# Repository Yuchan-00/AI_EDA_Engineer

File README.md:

# AI EDA ENGINEER

**English** · [한국어](README.ko.md)

A **verification-first** AI engineering system for electronic circuit design. It takes a natural-language requirement through one pipeline:

`requirements` → `parts & regulatory research` → `Universal Circuit IR` → `calculations / SPICE` → `KiCad schematic & PCB` → `ERC / DRC` → `manufacturing outputs` → `independent review` → `auto-fix`

> **Core principle: the LLM never decides design truth.** It only proposes and orchestrates. Facts come from the IR, provenance, deterministic tools (calculators, SPICE, KiCad ERC/DRC, manufacturing-file checks) and an independent reviewer.

This page is an English overview. The full reference — every stage, check, option, measured result and the change history — is the Korean [README.ko.md](README.ko.md). The generated stage reports and the local web GUI are in Korean; the read-only HTML report (`ai-eda report`) is in English.

## Quick install

**macOS / Linux (Ubuntu, Debian, Arch, Fedora)** — in a terminal:

```bash
curl -fsSL https://raw.githubusercontent.com/Yuchan-00/AI_EDA_Engineer/main/install.sh | bash
```

**Windows 10 / 11** — in PowerShell:

```powershell
powershell -ExecutionPolicy Bypass -c "irm https://raw.githubusercontent.com/Yuchan-00/AI_EDA_Engineer/main/install.ps1 | iex"
```

If you already have the repository, run `./install.sh` (macOS / Linux) or `install.cmd` (Windows) in its folder.

- The installer sets up a uv-managed Python 3.12 environment, KiCad 10 (with libraries) and ngspice without asking. A browser for PDF reports is installed only on Linux when none is found; macOS and Windows use an existing Chrome or Edge.
- It puts `ai-eda` on your PATH and finishes with `ai-eda selftest`, which designs a 12 V → 5 V divider end to end to confirm the tools actually run.
- Do not run it with `sudo`; the script asks for an administrator password itself when it needs one (UAC on Windows).
- Debian stable has no KiCad 10 package: install with `--no-kicad`, then install KiCad 10 yourself. Options and per-OS details are in the Korean README (설치).

Then open a new terminal:

```bash
ai-eda doctor       # tools found (KiCad, ngspice, browser) and how to install what is missing
ai-eda gui --open   # local web GUI (Korean)
```

The install CI (GitHub Actions, 2026-10-14) installs, runs `doctor --strict` and `selftest` on ubuntu-24.04, ubuntu-22.04, macos-15, Arch Linux and windows-2025; on all five the selftest's divider board passed KiCad ERC/DRC with 0 errors / 0 warnings.

## Usage

```bash
ai-eda new demo --request "a circuit that converts 12 V input to 5 V"
ai-eda run projects/demo/ir.json
```

When required information is missing, the pipeline stops at `USER_INPUT_REQUIRED` and prints its questions. Answer with `--answer key=value` and run again:

```bash
ai-eda run projects/demo/ir.json --answer application="bench supply" --answer jurisdiction=EU \
  --answer input_voltage="12 V" --answer output_voltage="5 V"
```

A template's free choices (for example the divider's R2) are shown in a `confirm_design` table and applied only after you confirm it on a later run with `--answer confirm_design=yes`. Other commands: `review`, `report` / `serve` (read-only HTML report), `stage-reports` (Korean stage reports as Markdown, HTML and PDF), `relocate` (re-record a copied or moved project), `setup-kicad`.

## What it does

| Layer | What it is |
|---|---|
| **Universal Circuit IR** | Pydantic v2 model of the project, requirements, components, pins, nets, topology, constraints, PCB, regulatory scope, validation and artifacts. The design hash covers design content only, so the same design gets the same hash anywhere. |
| **Provenance** | Every important value is `Traced[T]`: `user_requirement`, `authoritative`, `assumption`, `derived` or `llm_generated`. |
| **Validation status** | `PASS / FAIL / NOT_VERIFIED / NOT_APPLICABLE / USER_INPUT_REQUIRED / UNRESOLVED`, aggregated conservatively. No evidence means `NOT_VERIFIED`, never `PASS`. |
| **Calculators** | Deterministic, registered calculators (Ohm's law, dividers, RC, LED resistors, power, junction temperature, transmission lines, RF matching and filters, ...) whose results are recomputed and checked. |
| **SPICE** | ngspice through KiCad's bundled library (ctypes): operating point, DC sweep, transient and AC analyses, judged against expected values with explicit tolerances or one-sided bounds. |
| **KiCad** | Compilers from the IR to `.kicad_sch`, `.kicad_pcb` and `.kicad_pro`, using symbols and footprints read from the installed KiCad libraries (never from model memory); ERC/DRC through `kicad-cli`, where any violation, warnings included, is a FAIL. |
| **Layout** | Deterministic placement (grid, core-ring, RF floorplan), a grid maze router with negotiated congestion, silkscreen placement, a built-in 3D preview, and need-driven signal-integrity checks (impedance, critical length, RF length). |
| **Manufacturing** | Gerber / drill export with format checks, BOM and CPL, and fab-capability limits grounded verbatim from an archived vendor page. |
| **Parts & regulatory** | Part existence checks against libraries and archived datasheets, datasheet-fact grounding, catalog import, and curated regulatory candidates (EU and KR) with deterministic applicability. Sources are fetched only with `--online` from trusted origins and archived with sha256. Regulatory *compliance* is never claimed (`NOT_VERIFIED`). |
| **Templates** | Deterministic circuit templates: unloaded resistor divider, LED + series resistor, first-order RC low-pass, BJT astable, ATmega128 dev board, and five KR 447 MHz radio boards (`radio_build`). |
| **Agents & LLM** | Ten agents that only propose; the orchestrator validates and applies proposals. LLMs (OpenRouter with a budget flag as approval, or your local Claude Code CLI) extract requirements and suggest parts; every model output must be grounded and then confirmed by you on a later run before it enters the IR. |
| **Review & repair** | An independent reviewer covering 14 areas, and an auto-repair loop that only regenerates artifacts or re-runs tools. Design changes need a human. |
| **Approval gate** | Outward-facing actions (paid model calls, network fetches, secrets, git push, orders, submissions) go through an explicit approval gate. |

## Known limits

- Component suitability is judged for electrical stress only (nominal values, one operating point, one temperature). Safety, regulatory compliance, environment, reliability, manufacturability, sourcing and cost are not evaluated by any code.
- Several KiCad canary tests (silkscreen DRC, 3D export, sibling project rules) have not yet run on a KiCad machine; until they do, the checks that depend on them stay `NOT_VERIFIED` by design. The only routed board whose real DRC has run is the selftest's divider in the install CI.
- Board impedance is computed quasi-statically and losslessly; only a fab's coupon measurement can confirm it.

The full list, with the reason each limit exists, is in [README.ko.md](README.ko.md).

## Project layout

```
ai_eda/
  ir/            Universal Circuit IR, provenance, validation status
  validation/    validators and their registry
  design/        deterministic circuit templates (rf/: KR 447 MHz radio family)
  tools/         calculators, ngspice runner, KiCad parser / libraries / kicad-cli wrapper,
                 placement, routing, silkscreen, 3D preview, manufacturing, source archive
  parts/         part existence, identity grounding, datasheet facts, catalog
  regulatory/    curated candidates, applicability, official-source research
  compilers/     IR → .kicad_sch / .kicad_pcb / .kicad_pro / BOM / CPL / SPICE netlist
  agents/        agents (propose only)
  llm/           model layer (OpenRouter, Claude Code CLI, budget, extraction)
  review/        independent reviewer (14 areas)
  repair/        deterministic repair strategies and closed loop
  report/, gui/  read-only HTML report, Korean stage reports, local web GUI
  workflow/      19-stage pipeline and orchestrator
  security/      approval gate for outward-facing actions
  cli.py         doctor / setup-kicad / selftest / new / run / review / relocate / report / serve / stage-reports / gui
tests/           test suite (tool tests skip when KiCad / ngspice are missing)
docs/ARCHITECTURE.md   spec ↔ module map and invariants (Korean)
install.sh, install.ps1, install.cmd   one-line installers
```

Run the tests with `python -m pytest -q -p no:cacheprovider -rs`. Without KiCad and ngspice the tool tests skip, and a green run without them is not tool verification.

## License

MIT License with the Commons Clause License Condition v1.0, see [LICENSE](LICENSE). You may use, copy, modify and share this software free of charge; you may not sell it, or a product or service whose value comes substantially from it (hosting and paid support included), without a separate agreement with the author. Because of that restriction it is source-available rather than OSI-approved open source.

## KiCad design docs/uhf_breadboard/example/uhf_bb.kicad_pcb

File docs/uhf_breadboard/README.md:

# UHF FM 무전기 (만능기판·브레드보드 실험용, 아마추어 430–440 MHz)

이 문서는 `radio_build = uhf_breadboard` 템플릿(`ai_eda/design/rf/t_breadboard.py`)이 만드는 무전기를 손으로 조립하기 위한 안내서입니다. 상용급이 아니라 **실험해서 동작을 확인하는 수준**이 목표입니다. 프로그래머블 소자(마이컴, PLL, FM 송수신 모듈)는 쓰지 않고, 트랜지스터와 연산증폭기로만 만듭니다.

> **먼저 읽을 것 — 법규**
> - 직접 만든 송신기는 KC 적합성평가를 받지 않았습니다. **생활무선(447 MHz 면허 면제) 채널에서는 절대 송신하지 않습니다.**
> - 이 무전기는 **아마추어 무선국 허가** 조건 안에서, 430–440 MHz 아마추어 대역의 허가된 주파수·출력·전파형식으로만 씁니다. 국내 아마추어 대역 사용계획과 허가 조건은 이 문서에서 확인하지 못했습니다 [UNVERIFIED].
> - 안테나를 달기 전에 반드시 **50 Ω 더미로드**에 연결하고 불요발사(스퓨리어스)를 확인합니다(아래 조정 순서 6단계).

## 1. 전체 구성

```
           ┌──────────── 송신 (TX/RX 스위치를 TX로) ─────────────────────────────────────────────┐
 마이크 → TL071 증폭(+다이오드 리미터) → TL071 저역통과(3 kHz) → 편이 트리머 → 가변용량 다이오드
                                                                                │
   36 MHz 수정 VXO(2N3904) → ×3 BF199(108 MHz) → ×2 BFR92A(216 MHz) → ×2 BFR92A(432 MHz)
   → 3공진기 대역통과 → A급 출력단 BFR92A(약 30 mW) → L 정합 → 5차 저역통과 → T/R 스위치 → SMA
                                                                                │
           ┌──────────── 수신 (TX/RX 스위치를 RX로) ────────────────────────────┘
 SMA → T/R(λ/4) → 공통 베이스 RF 증폭 BFR92A → 초재생 검파 BFR92A(자기 소멸 약 190 kHz)
     → TL071 증폭 → TL071 저역통과(3 kHz, 소멸 신호 제거) → 볼륨 → TL071 + BD139/BD140 → 스피커 8 Ω
```

| 블록 | 부품 번호 | 내용 |
|---|---|---|
| 전원 | 1xx | 9 V 배터리, 전원 스위치, 1N5817(역접속 보호), TX/RX 슬라이드 스위치, L78L05 두 개(V5T 송신용, V5R 수신용) |
| 송신 오디오 | 2xx | 일렉트릿 마이크, TL071 ×2, 소프트 리미터 1N4148 ×2, 편이 트리머 RV201, 가변용량 바이어스 |
| 송신 RF | 3xx | 수정 VXO, ×3·×2·×2 체배기, 3공진기 대역통과(CT304–CT306), 출력단, L 정합, 5차 저역통과 |
| T/R 스위치 | 6xx | 1N4148 직렬/병렬, 집중정수 λ/4(L601, C601, C602), SMA J601 |
| 수신 RF | 4xx | 공통 베이스 RF 증폭 Q401, 초재생 검파 Q402, 재생 트리머 RV401, 동조 트리머 CT401 |
| 수신 오디오 | 5xx | TL071 ×3, 볼륨 RV501, BD139/BD140 출력단, 스피커 J501 |

- **채널:** 하나로 고정입니다. 수정 주파수 = 반송파 ÷ 12입니다. 36.000 MHz 기성품을 쓰면 432.000 MHz가 되고, 다른 주파수는 수정을 주문 제작합니다(기본파 모드, HC-49/U). 432.000 MHz가 국내 아마추어 대역 사용계획에서 FM 송신에 맞는 주파수인지는 확인이 필요합니다.
- **설계 근거:** 433.92 MHz SAW 발진기도 검토했습니다. 하지만 ngspice 시뮬레이션에서 SAW의 C0를 통해 505 MHz로 자유 발진하거나 아예 기동하지 않아, 수정 ×12 방식을 택했습니다. 36 MHz 수정 VXO는 기동 여유가 약 3배입니다.

## 2. 이 저장소에서 만들어지는 것

```bash
ai-eda new uhf_bb --dir ./uhf_bb
ai-eda run ./uhf_bb/ir.json --answer radio_build=uhf_breadboard --answer "carrier_frequency=432 MHz" \
   --answer modulation=FM --answer "input_voltage=9 V" --answer application=amateur_radio_experiment --answer jurisdiction=KR
ai-eda run ./uhf_bb/ir.json --answer confirm_design=yes     # 표를 확인한 뒤
```

결과 폴더에는 다음이 생깁니다.

- KiCad 회로도(`.kicad_sch`)와 2층 PCB(`.kicad_pcb`, 200 × 100 mm, 블록별 영역에 배치·배선)
- BOM, 부품 좌표 파일(CPL), 거버
- 3D 미리보기
- 한국어 단계 보고서 4종(`reports/`)

이 PCB는 만능기판 대신 기판을 주문해 실험하고 싶을 때 쓰는 대안입니다. KiCad ERC/DRC는 kicad-cli가 있는 PC에서 실행해야 합니다.

**이 폴더에 들어 있는 것** (2026-11-03, KiCad 10.0.6 라이브러리, ngspice-42 실행 결과):

- `example/`: 432.000 MHz, 9 V로 만든 회로도, PCB, 프로젝트 파일, BOM, CPL, 이론·회로·최종 보고서(`.md`)
- `board.svg`: 배선된 기판 그림(배선 1334개, 비아 56개, 84개 넷 모두 연결)
- `wiring.md`: **배선표.** 블록별로 각 넷에 연결할 핀(`R301.1`, `Q301.2(B)` …)을 나열합니다. 컴파일된 회로도는 기호를 선 대신 넷 이름표로 잇기 때문에, 납땜할 때는 이 표를 기준으로 합니다.
- `perfboard_all.svg`, `perfboard_<블록>.svg`: 만능기판 배치도. PCB 배치를 2.54 mm 격자로 옮긴 그림입니다. 각 블록 안에서 부품이 신호 순서대로 줄지어 놓입니다(송신 RF는 VXO → ×3 → ×2 → ×2·대역통과 → 출력단·저역통과 순서로 한 줄씩).
  - 선 색: 빨강 전원, 파랑 RF, 회색 일반 신호. 접지 기호는 접지 버스에 연결한다는 뜻입니다.
  - 그림 안의 선은 연결 관계를 나타낼 뿐, 실제 배선 경로가 아닙니다.

배치도와 배선표는 다음 명령으로 다시 만듭니다.

```bash
python docs/uhf_breadboard/make_perfboard_svg.py ./uhf_bb/ir.json docs/uhf_breadboard/
```

## 3. 브레드보드 → 만능기판 순서

432 MHz는 브레드보드에서 동작하지 않습니다. 브레드보드는 줄 사이 용량(수 pF)과 접점 인덕턴스 때문에 엉뚱한 회로가 됩니다. 그래서 아래 순서로 나눠서 만듭니다.

| 단계 | 어디에 | 무엇을 | 확인 |
|---|---|---|---|
| 1 | 브레드보드 | 전원부: 9 V, 1N5817, 스위치 두 개, L78L05 두 개 | V5T·V5R이 5 V인지(멀티미터) |
| 2 | 브레드보드 | 수신 오디오: TL071 ×3, BD139/BD140, 볼륨, 스피커 | AF_RAW에 1 kHz 5 mV를 넣고 스피커에서 소리가 나는지. 출력 직류 약 4.5 V |
| 3 | 브레드보드 | 송신 오디오: 마이크, TL071 ×2, 편이 트리머 | 마이크에 대고 말할 때 TXA에 0.5–1 Vpp, 큰 소리에 ±0.6 V 근처에서 클리핑 |
| 4 | 만능기판(동판 접지 권장) | VXO와 ×3 단 | 주파수 카운터나 SDR로 36 MHz와 108 MHz 확인 |
| 5 | 만능기판 | ×2, ×2, 대역통과, 출력단, 저역통과, T/R | 더미로드에서 432 MHz 출력 |
| 6 | 만능기판 | 초재생 수신부 | 재생 트리머로 '쉬' 잡음이 나는 지점, 근처 송신기 신호 수신 |

검증된 오디오·전원부는 브레드보드에서 만능기판으로 옮겨도 되고, 브레드보드에 둔 채 짧은 선으로 이어도 됩니다.

**만능기판 요령 (RF 단):**

- **접지:** 기판 한 면 전체를 접지로 씁니다. 동박 기판을 조각내 붙이거나, 굵은 주석선으로 접지 버스를 만듭니다. 모든 바이패스 커패시터의 접지 리드는 1–2 mm 이내로 짧게 합니다. 432 MHz에서는 선 1 mm가 약 1 nH입니다.
- **BFR92A:** SOT-23이므로 SOT-23→DIP 변환 기판에 올리거나, 동판 위에 '데드버그'로 직접 납땜합니다.
- **트리머:** 라이브러리에 THT 트리머가 없어 KiCad 기판은 Murata TZC3(SMD)입니다. 만능기판에는 같은 범위의 THT 세라믹 트리머(2–10 pF, 3–20 pF 등)를 씁니다.
- **0.2 pF 결합:** 대역통과의 결합 C319·C320(약 0.18 pF)은 기성품이 없습니다. 절연 전선 두 가닥을 1–2 cm 꼬은 '기믹' 커패시터로 만들고, 조정 중에 길이를 잘라 맞춥니다. 탭 C318·C321(약 0.6 pF)은 0.5 pF 부품에 기믹을 더하거나, 같은 방법으로 만듭니다.
- **블록 사이 배치:** 단과 단 사이는 일렬로 놓고, 출력단과 VXO는 서로 멀리 둡니다.

## 4. 코일 감기 (어림값, 측정해서 맞출 것)

Wheeler 공식으로 계산한 공심 코일 값입니다. 에나멜선 0.6–0.8 mm, 표의 지름은 선 중심 기준입니다. 실제 인덕턴스는 리드 길이와 감는 간격에 따라 ±30 % 이상 달라지므로, 트리머 범위 안에 들어오는지 공진으로 확인합니다 [UNVERIFIED].

| 부품 | 용도 | 값 | 감는 법(어림) |
|---|---|---|---|
| L306–L308 | 대역통과 공진 코일 | 15 nH | 지름 4 mm, 약 2턴, 간격 1.2 mm |
| L601 | λ/4 직렬 코일 | 18.4 nH | 지름 4 mm, 약 2.5턴 |
| L401 | 초재생 탱크 | 22 nH | 지름 4 mm, 약 2.7턴 |
| L311, L312 | 저역통과 직렬 코일 | 22.7 nH | 지름 4 mm, 약 2.7턴 |
| L310 | 출력 L 정합 | 66.6 nH | 지름 5 mm, 약 4턴 |
| L304 | ×2(216 MHz) 탱크 | 68 nH | 지름 5 mm, 약 4.3턴 |
| L302 | ×3(108 MHz) 탱크 | 150 nH | 지름 5 mm, 약 8턴 |
| L301, L303, L305, L309, L602, L402 | 급전·RF 초크 | 100 nH–1 µH | 작은 페라이트 비드에 가는 선 6–10턴, 또는 공심 3 mm 20–35턴 |

## 5. 조정 순서

**필요한 장비:**

- 멀티미터
- 50 Ω 더미로드(1 W, 무유도 저항 51 Ω 또는 100 Ω 두 개 병렬)
- 다이오드 RF 프로브
- 주파수 카운터 또는 RTL-SDR(스펙트럼 확인용)
- 가능하면 아마추어 핸디 무전기

1. **전원:** TX/RX 스위치를 각 위치에 두고 V5T·V5R이 5 V인지 확인합니다. TX일 때 배터리 전류는 대략 수십 mA입니다.
2. **VXO:** RF 단 급전 저항 R307 이후를 떼어 두고 VXO만 켭니다. 36 MHz(f_c/12)에 발진하는지 SDR로 확인하고, CT301로 중심 주파수를 맞춥니다. 수정 기본파의 끌림 폭은 수 kHz입니다.
3. **×3 탱크:** CT302로 108 MHz가 최대가 되게 맞춥니다. 72 MHz나 144 MHz에 맞추지 않도록 SDR로 주파수를 확인합니다.
4. **×2 탱크:** CT303으로 216 MHz를 최대로 맞춥니다.
5. **대역통과:** CT304 → CT305 → CT306 순서로 432 MHz를 최대로 맞춘 뒤, 처음부터 한 번 더 반복합니다. 그래도 출력이 너무 작으면 결합 기믹 C319·C320을 조금 길게 합니다.
6. **출력과 스퓨리어스(안테나 없이):** J601에 더미로드를 답니다. 출력단 Q305가 손으로 만졌을 때 뜨겁지 않은지(약 0.15 W 소모) 확인합니다. SDR로 396 MHz(f_c − f_X), 468 MHz(f_c + f_X), 864 MHz(2차 고조파)가 432 MHz보다 충분히 낮은지 봅니다. ngspice 고정 회로망 계산으로 대역통과는 각각 약 −45 dB, −35 dB(432 MHz 대비)이고, 저역통과는 2차 고조파에서 약 −29.5 dB, 3차에서 약 −49 dB입니다(코일 Q 80 가정). 허가 조건의 불요발사 기준을 만족하기 전에는 안테나를 달지 않습니다.
7. **편이:** 아마추어 핸디로 수신하면서 RV201을 조정합니다. 목소리가 찌그러지지 않는 최소 편이가 목표로, 협대역 ±2.5 kHz 또는 광대역 ±5 kHz 중 허가 조건에 맞춥니다.
8. **수신:**
   1. RV401을 돌려 스피커에서 '쉬—' 하는 초재생 잡음이 막 들리기 시작하는 지점에 둡니다.
   2. 다른 무전기로 432 MHz를 송신하고, CT401을 돌려 잡음이 줄어들며 신호가 들리는 지점을 찾습니다.
   3. FM은 정확히 반송파에 맞추면 잘 안 들립니다. 조금 비켜 맞추는 기울기 검파로 소리가 납니다.

## 6. 검증 범위 (파이프라인이 확인한 것과 아닌 것)

**ngspice로 확인한 것** (일반 모델 카드 기준의 원리 검증이며, 실제 부품 측정이 아님):

- 오디오 증폭 이득(1 kHz)
- 3 kHz Sallen-Key 저역통과 응답
- 기준 전압과 가변용량 바이어스
- 출력단 직류점과 이득
- 소멸 주파수(190 kHz)에서의 감쇠
- RF 수동 회로망: 체배 탱크 2개, 대역통과, L 정합, 저역통과, T/R 스위치(송신/수신 상태)

**실험 항목** (`ir.rf.lab_items`): VXO 기동과 주파수, 체배기 구동, 출력 전력, 불요발사, 초재생 수신 감도와 소멸, 스피커 출력, T/R 손실

- 1N4148은 PIN 다이오드가 아니므로 T/R 스위치의 실제 손실·격리는 측정해야 합니다.
- 일렉트릿 마이크의 극성은 PUI Audio 데이터시트와 대조하지 않았습니다 [UNVERIFIED].

## 7. 부품표

부품표는 실행 결과 폴더의 BOM 파일이 기준입니다. 대표 반도체는 다음과 같습니다.

- 트랜지스터: 2N3904 ×1, BF199 ×1, BFR92A ×6, BD139 ×1, BD140 ×1
- 연산증폭기: TL071 ×5
- 다이오드: 1N4148 ×6, 1N5817 ×1, BB910급 가변용량 다이오드 ×1
- 레귤레이터: L78L05 ×2
- 기타: 36.000 MHz(또는 f_c/12) 수정 ×1, 일렉트릿 마이크, 8 Ω 스피커, SMA 커넥터, 슬라이드 스위치 ×2

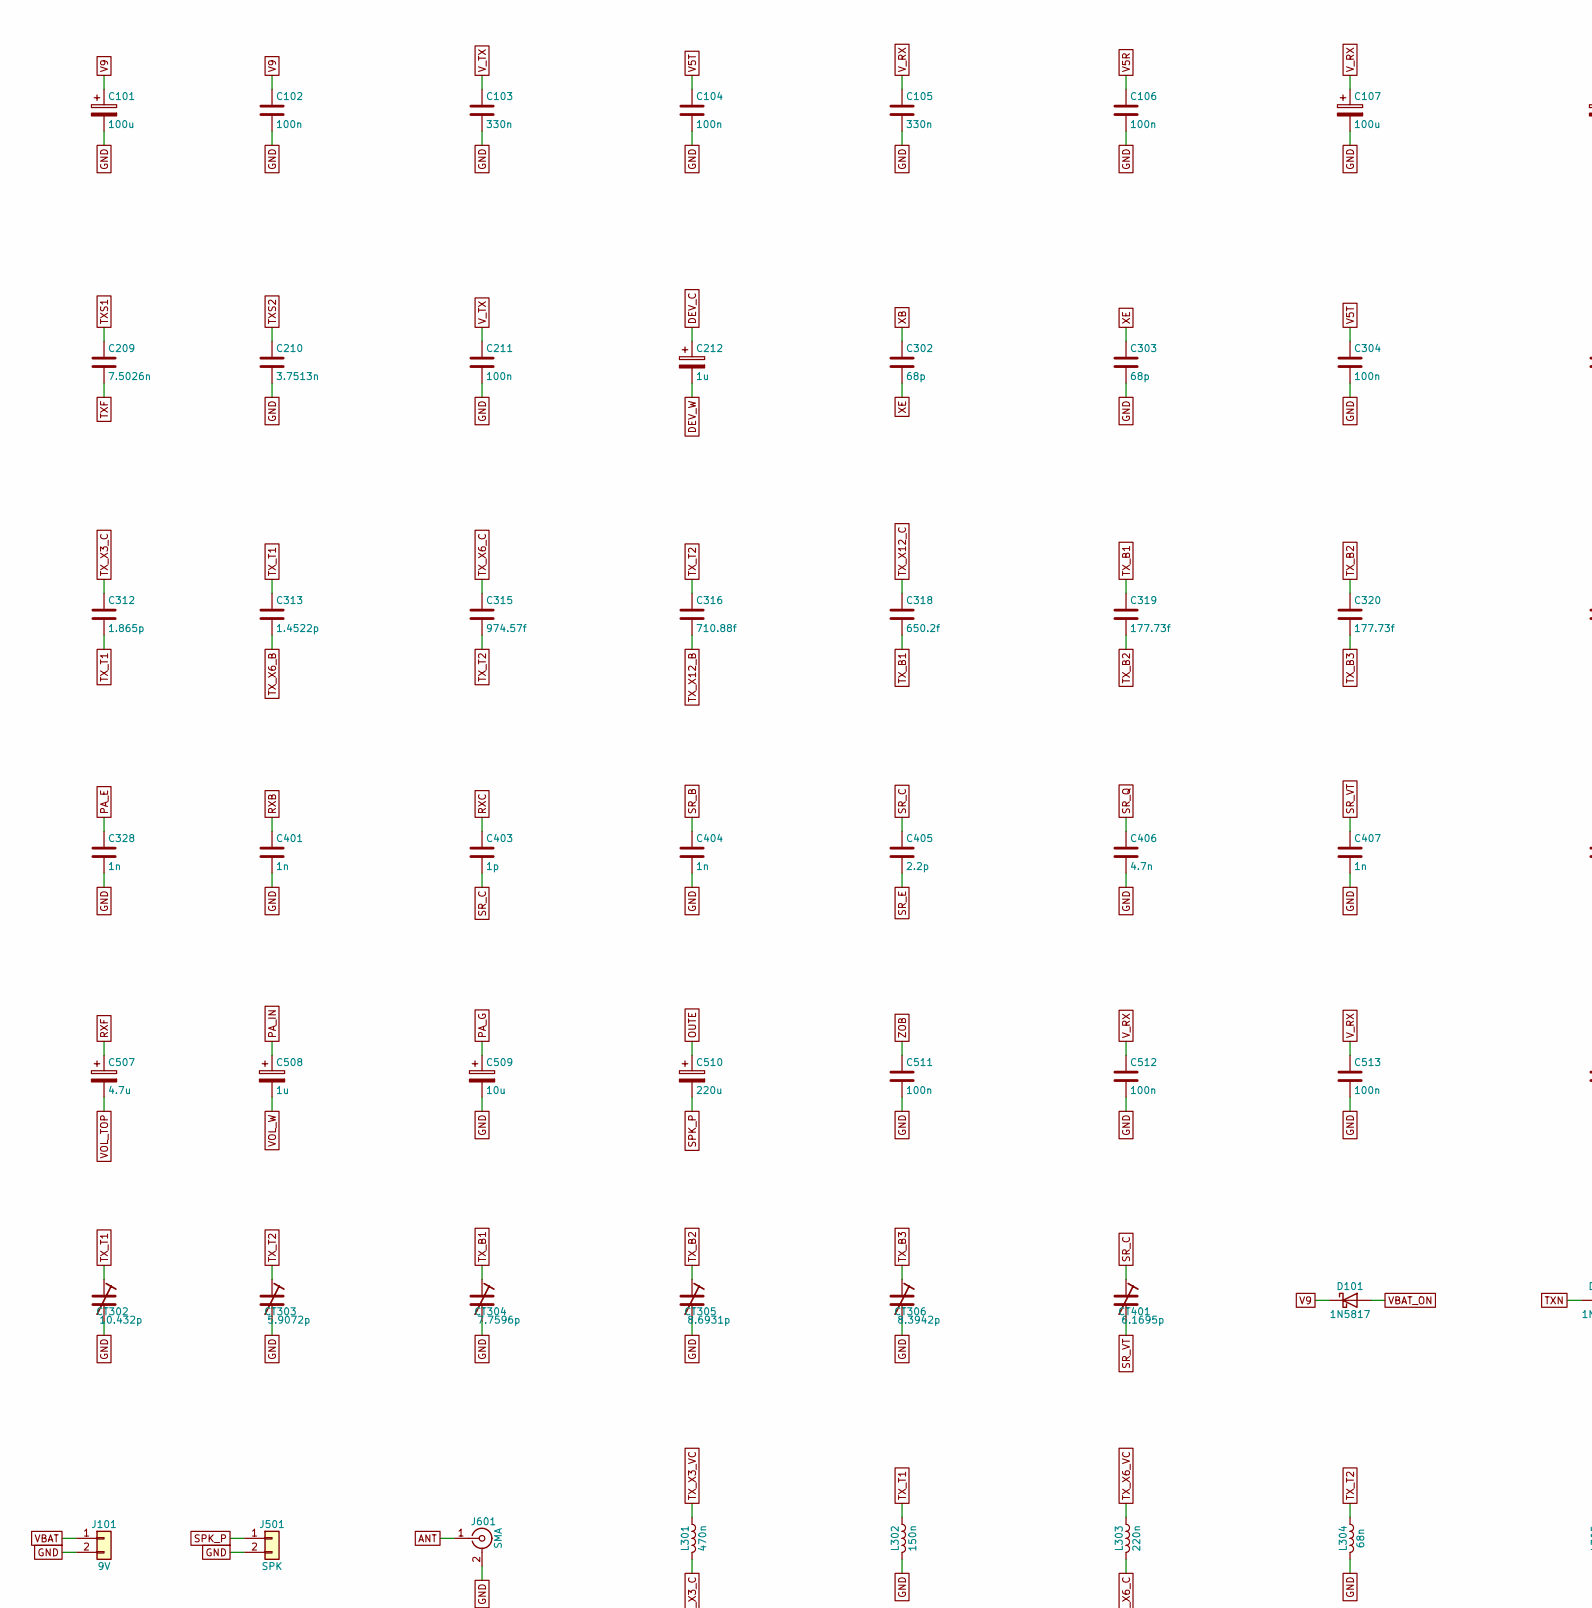
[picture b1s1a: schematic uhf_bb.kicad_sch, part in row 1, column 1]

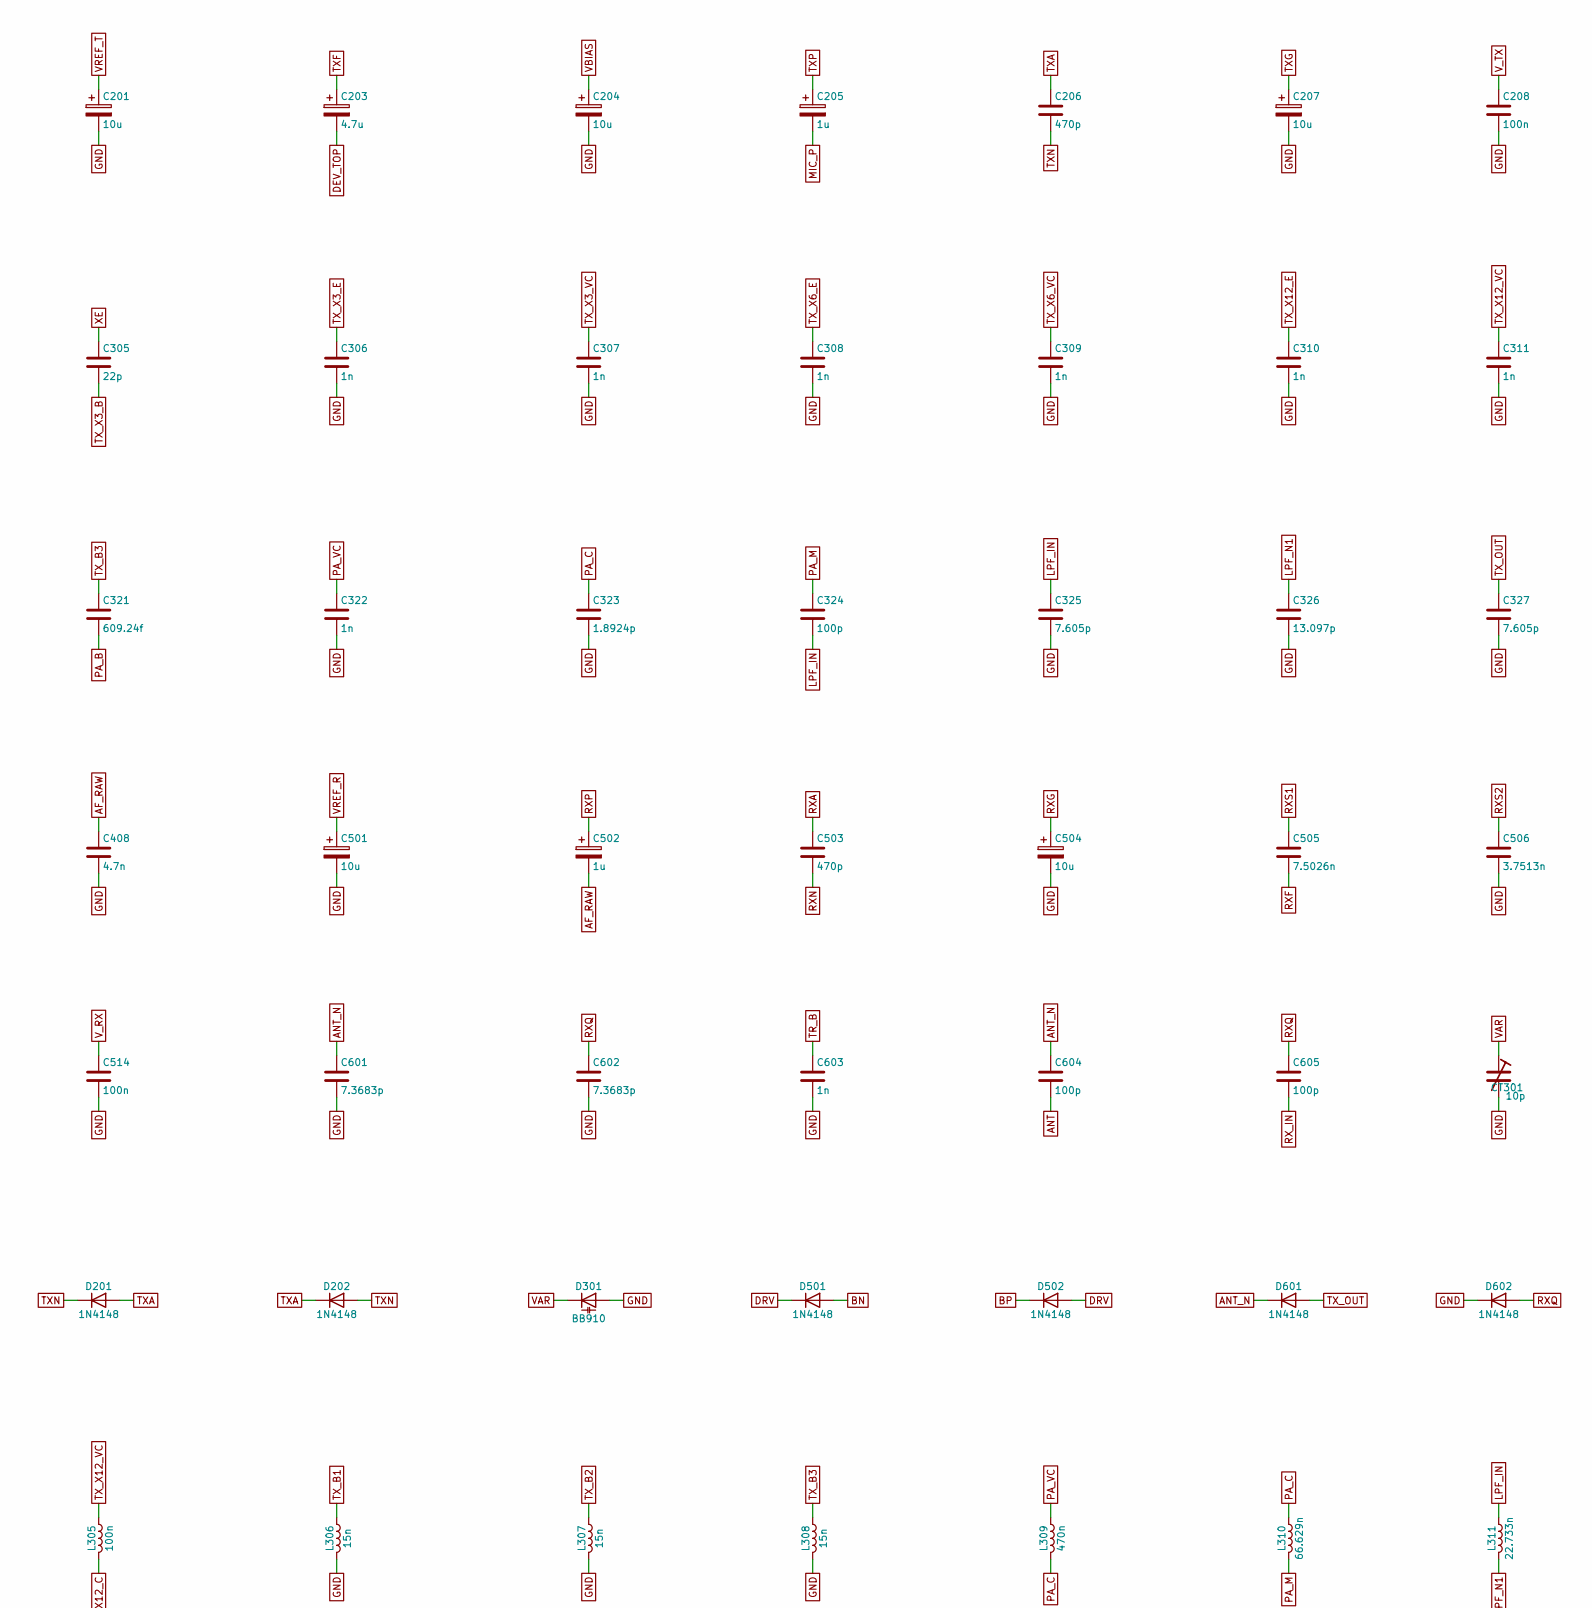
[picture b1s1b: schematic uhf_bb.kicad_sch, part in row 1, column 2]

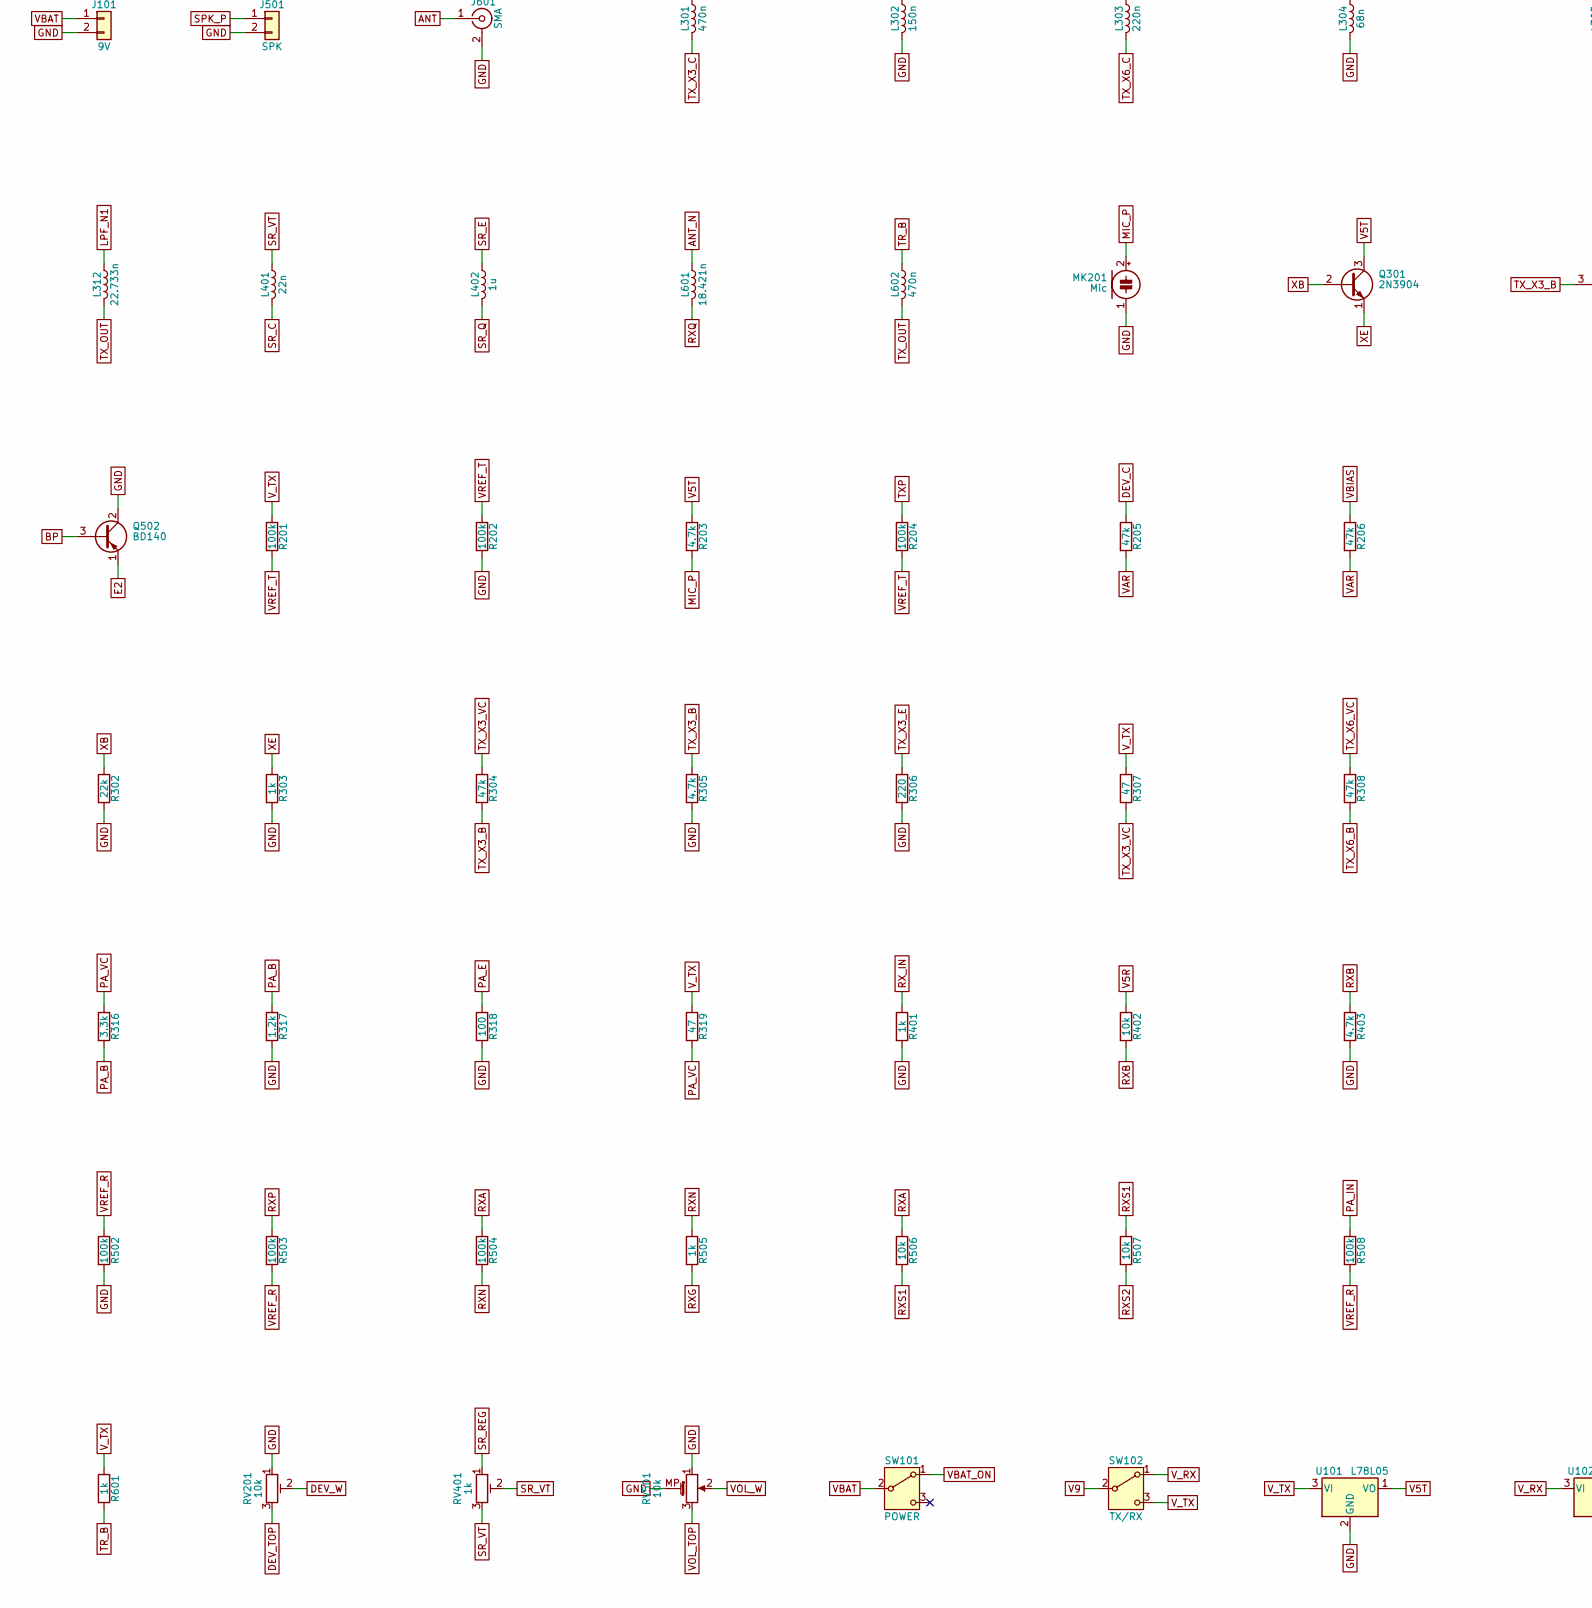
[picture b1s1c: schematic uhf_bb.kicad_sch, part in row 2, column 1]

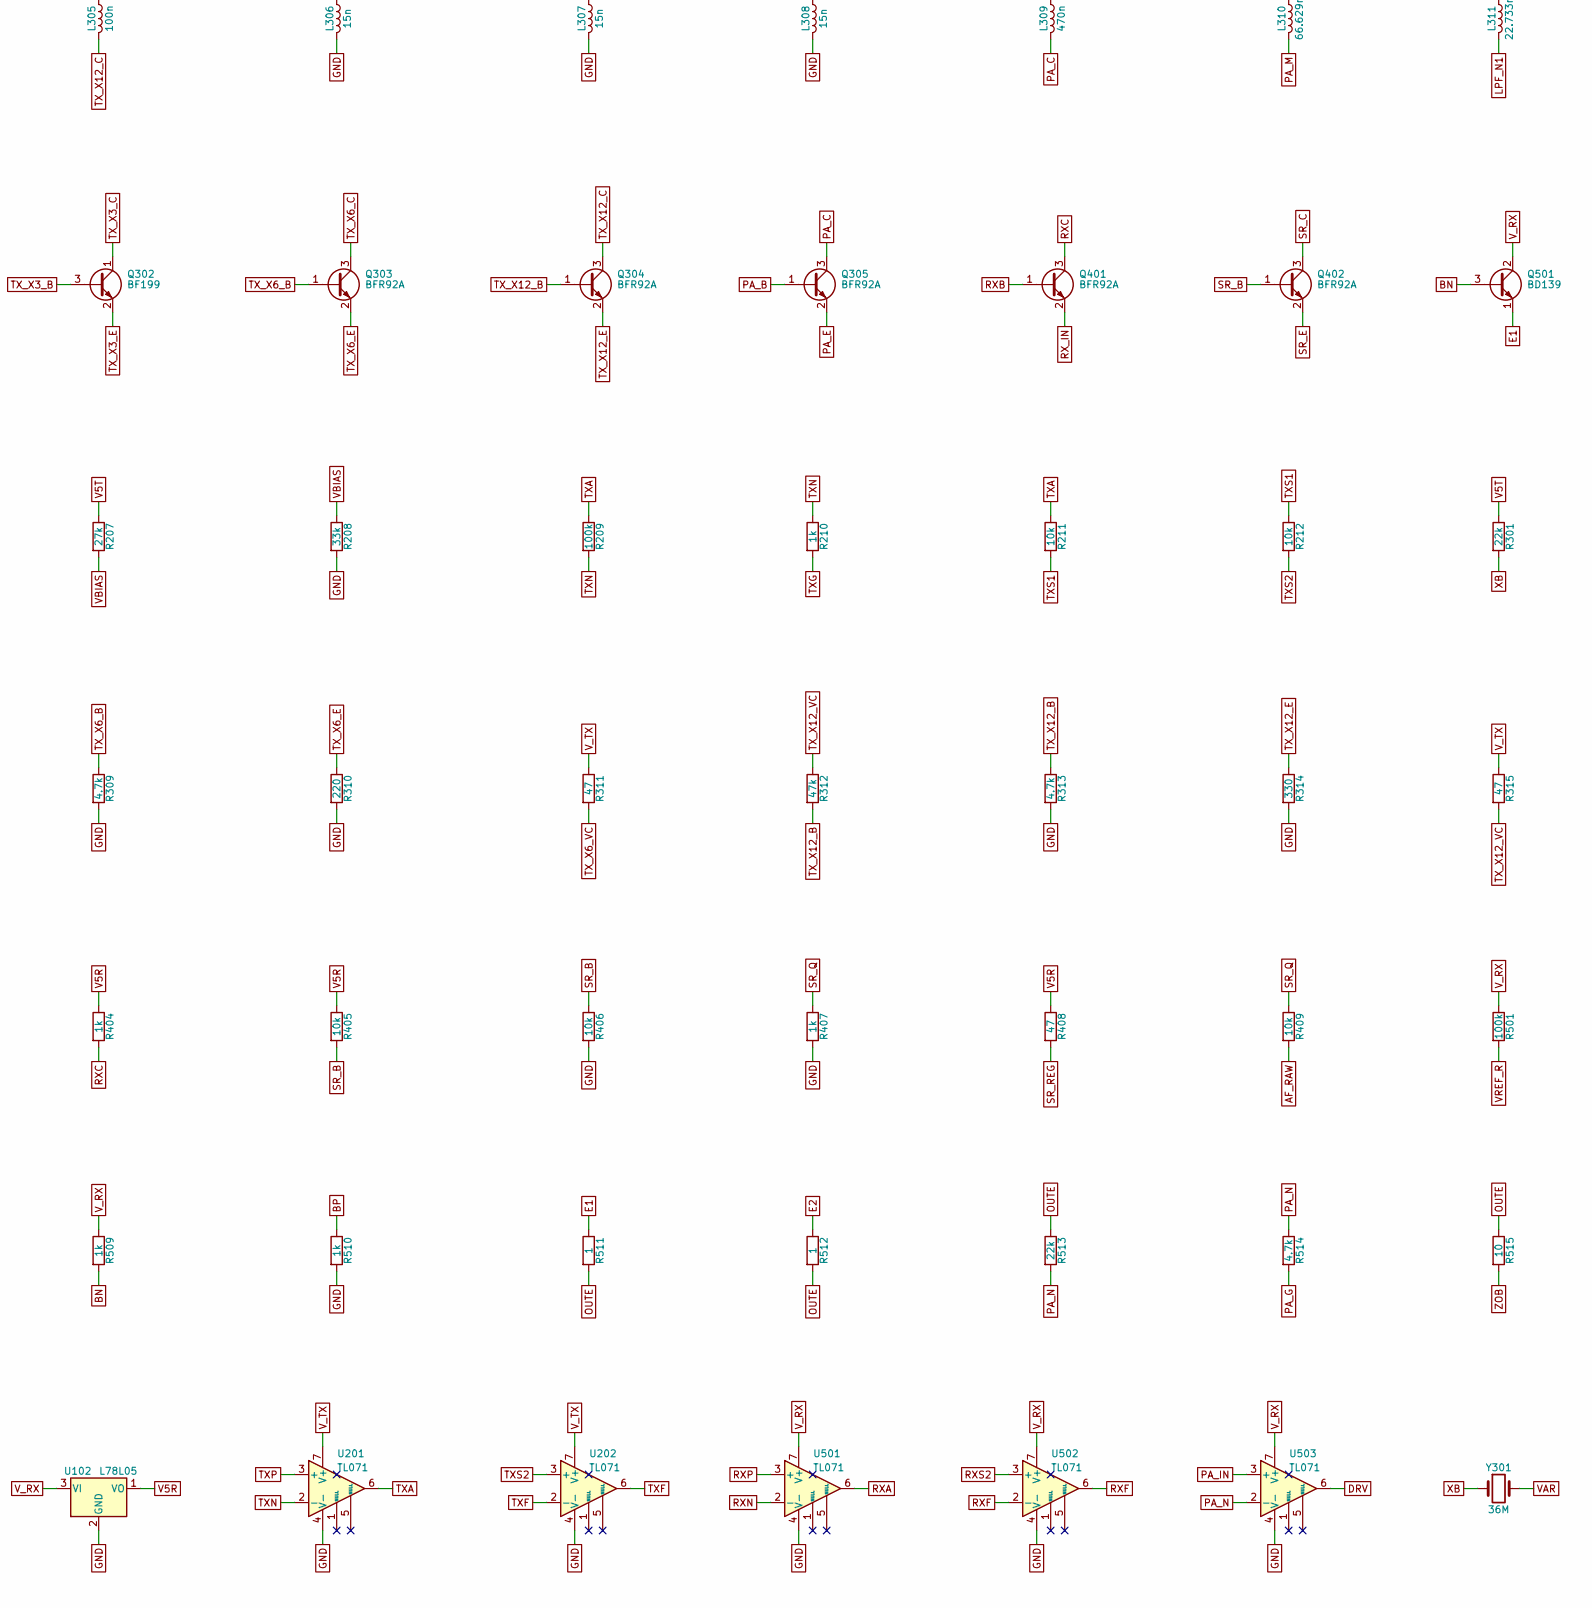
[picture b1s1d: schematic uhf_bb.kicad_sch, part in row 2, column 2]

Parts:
C101, C107: 100u; CP_Radial_D5.0mm_P2.00mm
C102, C104, C106, C208, C211, C304, C511, C512, C513, C514: 100n; C_Disc_D3.0mm_W1.6mm_P2.50mm
C103, C105: 330n; C_Disc_D3.0mm_W1.6mm_P2.50mm
C201, C204, C207, C501, C504, C509: 10u; CP_Radial_D5.0mm_P2.00mm
C203, C507: 4.7u; CP_Radial_D5.0mm_P2.00mm
C205, C212, C502, C508: 1u; CP_Radial_D5.0mm_P2.00mm
C206, C503: 470p; C_Disc_D3.0mm_W1.6mm_P2.50mm
C209, C505: 7.5026n; C_Disc_D3.0mm_W1.6mm_P2.50mm
C210, C506: 3.7513n; C_Disc_D3.0mm_W1.6mm_P2.50mm
C302, C303: 68p; C_Disc_D3.0mm_W1.6mm_P2.50mm
C305: 22p; C_Disc_D3.0mm_W1.6mm_P2.50mm
C306, C307, C308, C309, C310, C311, C322, C328, C401, C404, C407, C603: 1n; C_Disc_D3.0mm_W1.6mm_P2.50mm
C312: 1.865p; C_Disc_D3.0mm_W1.6mm_P2.50mm
C313: 1.4522p; C_Disc_D3.0mm_W1.6mm_P2.50mm
C315: 974.57f; C_Disc_D3.0mm_W1.6mm_P2.50mm
C316: 710.88f; C_Disc_D3.0mm_W1.6mm_P2.50mm
C318: 650.2f; C_Disc_D3.0mm_W1.6mm_P2.50mm
C319, C320: 177.73f; C_Disc_D3.0mm_W1.6mm_P2.50mm
C321: 609.24f; C_Disc_D3.0mm_W1.6mm_P2.50mm
C323: 1.8924p; C_Disc_D3.0mm_W1.6mm_P2.50mm
C324, C604, C605: 100p; C_Disc_D3.0mm_W1.6mm_P2.50mm
C325, C327: 7.605p; C_Disc_D3.0mm_W1.6mm_P2.50mm
C326: 13.097p; C_Disc_D3.0mm_W1.6mm_P2.50mm
C403: 1p; C_Disc_D3.0mm_W1.6mm_P2.50mm
C405: 2.2p; C_Disc_D3.0mm_W1.6mm_P2.50mm
C406, C408: 4.7n; C_Disc_D3.0mm_W1.6mm_P2.50mm
C510: 220u; CP_Radial_D5.0mm_P2.00mm
C601, C602: 7.3683p; C_Disc_D3.0mm_W1.6mm_P2.50mm
CT301: 10p; C_Trimmer_Murata_TZC3
CT302: 10.432p; C_Trimmer_Murata_TZC3
CT303: 5.9072p; C_Trimmer_Murata_TZC3
CT304: 7.7596p; C_Trimmer_Murata_TZC3
CT305: 8.6931p; C_Trimmer_Murata_TZC3
CT306: 8.3942p; C_Trimmer_Murata_TZC3
CT401: 6.1695p; C_Trimmer_Murata_TZC3
D101: 1N5817; D_DO-41_SOD81_P10.16mm_Horizontal
D201, D202, D501, D502, D601, D602: 1N4148; D_DO-35_SOD27_P7.62mm_Horizontal
D301: BB910; D_DO-35_SOD27_P7.62mm_Horizontal
J101: 9V; PinHeader_1x02_P2.54mm_Vertical
J501: SPK; PinHeader_1x02_P2.54mm_Vertical
J601: SMA; SMA_Amphenol_132134_Vertical
L301, L309, L602: 470n; L_Axial_L5.3mm_D2.2mm_P7.62mm_Horizontal_Vishay_IM-1
L302: 150n; L_Axial_L5.3mm_D2.2mm_P7.62mm_Horizontal_Vishay_IM-1
L303: 220n; L_Axial_L5.3mm_D2.2mm_P7.62mm_Horizontal_Vishay_IM-1
L304: 68n; L_Axial_L5.3mm_D2.2mm_P7.62mm_Horizontal_Vishay_IM-1
L305: 100n; L_Axial_L5.3mm_D2.2mm_P7.62mm_Horizontal_Vishay_IM-1
L306, L307, L308: 15n; L_Axial_L5.3mm_D2.2mm_P7.62mm_Horizontal_Vishay_IM-1
L310: 66.629n; L_Axial_L5.3mm_D2.2mm_P7.62mm_Horizontal_Vishay_IM-1
L311, L312: 22.733n; L_Axial_L5.3mm_D2.2mm_P7.62mm_Horizontal_Vishay_IM-1
L401: 22n; L_Axial_L5.3mm_D2.2mm_P7.62mm_Horizontal_Vishay_IM-1
L402: 1u; L_Axial_L5.3mm_D2.2mm_P7.62mm_Horizontal_Vishay_IM-1
L601: 18.421n; L_Axial_L5.3mm_D2.2mm_P7.62mm_Horizontal_Vishay_IM-1
MK201: Mic; POM-2244P-C3310-2-R
Q301: 2N3904; TO-92_Inline
Q302: BF199; TO-92_Inline
Q303, Q304, Q305, Q401, Q402: BFR92A; SOT-23
Q501: BD139; TO-126-3_Vertical
Q502: BD140; TO-126-3_Vertical
R201, R202, R204, R209, R501, R502, R503, R504, R508: 100k; R_Axial_DIN0207_L6.3mm_D2.5mm_P7.62mm_Horizontal
R203, R305, R309, R313, R403, R514: 4.7k; R_Axial_DIN0207_L6.3mm_D2.5mm_P7.62mm_Horizontal
R205, R206, R304, R308, R312: 47k; R_Axial_DIN0207_L6.3mm_D2.5mm_P7.62mm_Horizontal
R207: 27k; R_Axial_DIN0207_L6.3mm_D2.5mm_P7.62mm_Horizontal
R208: 33k; R_Axial_DIN0207_L6.3mm_D2.5mm_P7.62mm_Horizontal
R210, R303, R401, R404, R407, R505, R509, R510, R601: 1k; R_Axial_DIN0207_L6.3mm_D2.5mm_P7.62mm_Horizontal
R211, R212, R402, R405, R406, R409, R506, R507: 10k; R_Axial_DIN0207_L6.3mm_D2.5mm_P7.62mm_Horizontal
R301, R302, R513: 22k; R_Axial_DIN0207_L6.3mm_D2.5mm_P7.62mm_Horizontal
R306, R310: 220; R_Axial_DIN0207_L6.3mm_D2.5mm_P7.62mm_Horizontal
R307, R311, R315, R319, R408: 47; R_Axial_DIN0207_L6.3mm_D2.5mm_P7.62mm_Horizontal
R314: 330; R_Axial_DIN0207_L6.3mm_D2.5mm_P7.62mm_Horizontal
R316: 3.3k; R_Axial_DIN0207_L6.3mm_D2.5mm_P7.62mm_Horizontal
R317: 1.2k; R_Axial_DIN0207_L6.3mm_D2.5mm_P7.62mm_Horizontal
R318: 100; R_Axial_DIN0207_L6.3mm_D2.5mm_P7.62mm_Horizontal
R511, R512: 1; R_Axial_DIN0207_L6.3mm_D2.5mm_P7.62mm_Horizontal
R515: 10; R_Axial_DIN0207_L6.3mm_D2.5mm_P7.62mm_Horizontal
RV201: 10k; Potentiometer_Bourns_3386P_Vertical
RV401: 1k; Potentiometer_Bourns_3386P_Vertical
RV501: 10k; Potentiometer_Alps_RK09K_Single_Vertical
SW101: POWER; SW_Slide_SPDT_Straight_CK_OS102011MS2Q
SW102: TX/RX; SW_Slide_SPDT_Straight_CK_OS102011MS2Q
U101, U102: L78L05; TO-92_Inline
U201, U202, U501, U502, U503: TL071; DIP-8_W7.62mm
Y301: 36M; Crystal_HC49-U_Vertical

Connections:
AF_RAW: C408.1, C502.2, R409.2
ANT: C604.2, J601.1 (In)
ANT_N: C601.1, C604.1, D601.1 (K), L601.1
BN: D501.2 (A), Q501.3 (B), R509.2
BP: D502.1 (K), Q502.3 (B), R510.1
DEV_C: C212.1, R205.1
DEV_TOP: C203.2, RV201.3
DEV_W: C212.2, RV201.2
DRV: D501.1 (K), D502.2 (A), U503.6
E1: Q501.1 (E), R511.1
E2: Q502.1 (E), R512.1
GND: C101.2, C102.2, C103.2, C104.2, C105.2, C106.2, C107.2, C201.2, C204.2, C207.2, C208.2, C210.2, C211.2, C303.2, C304.2, C306.2, C307.2, C308.2, C309.2, C310.2, C311.2, C322.2, C323.2, C325.2, C326.2, C327.2, C328.2, C401.2, C404.2, C406.2, C407.2, C408.2, C501.2, C504.2, C506.2, C509.2, C511.2, C512.2, C513.2, C514.2, C601.2, C602.2, C603.2, CT301.2, CT302.2, CT303.2, CT304.2, CT305.2, CT306.2, D301.2 (A), D602.1 (K), J101.2, J501.2, J601.2 (Ext), L302.2, L304.2, L306.2, L307.2, L308.2, MK201.1 (-), Q502.2 (C), R202.2, R208.2, R302.2, R303.2, R305.2, R306.2, R309.2, R310.2, R313.2, R314.2, R317.2, R318.2, R401.2, R403.2, R406.2, R407.2, R502.2, R510.2, RV201.1, RV501.1, RV501.MP (MountPin), U101.2 (GND), U102.2 (GND), U201.4 (V-), U202.4 (V-), U501.4 (V-), U502.4 (V-), U503.4 (V-)
LPF_IN: C324.2, C325.1, L311.1
LPF_N1: C326.1, L311.2, L312.1
MIC_P: C205.2, MK201.2 (+), R203.2
OUTE: C510.1, R511.2, R512.2, R513.1, R515.1
PA_B: C321.2, Q305.1 (B), R316.2, R317.1
PA_C: C323.1, L309.2, L310.1, Q305.3 (C)
PA_E: C328.1, Q305.2 (E), R318.1
PA_G: C509.1, R514.2
PA_IN: C508.1, R508.1, U503.3 (+)
PA_M: C324.1, L310.2
PA_N: R513.2, R514.1, U503.2 (-)
PA_VC: C322.1, L309.1, R316.1, R319.2
RXA: C503.1, R504.1, R506.1, U501.6
RXB: C401.1, Q401.1 (B), R402.2, R403.1
RXC: C403.1, Q401.3 (C), R404.2
RXF: C505.2, C507.1, U502.2 (-), U502.6
RXG: C504.1, R505.2
RXN: C503.2, R504.2, R505.1, U501.2 (-)
RXP: C502.1, R503.1, U501.3 (+)
RXQ: C602.1, C605.1, D602.2 (A), L601.2
RXS1: C505.1, R506.2, R507.1
RXS2: C506.1, R507.2, U502.3 (+)
RX_IN: C605.2, Q401.2 (E), R401.1
SPK_P: C510.2, J501.1
SR_B: C404.1, Q402.1 (B), R405.2, R406.1
SR_C: C403.2, C405.1, CT401.1, L401.2, Q402.3 (C)
SR_E: C405.2, L402.1, Q402.2 (E)
SR_Q: C406.1, L402.2, R407.1, R409.1
SR_REG: R408.2, RV401.1
SR_VT: C407.1, CT401.2, L401.1, RV401.2, RV401.3
TR_B: C603.1, L602.1, R601.2
TXA: C206.1, D201.2 (A), D202.1 (K), R209.1, R211.1, U201.6
TXF: C203.1, C209.2, U202.2 (-), U202.6
TXG: C207.1, R210.2
TXN: C206.2, D201.1 (K), D202.2 (A), R209.2, R210.1, U201.2 (-)
TXP: C205.1, R204.1, U201.3 (+)
TXS1: C209.1, R211.2, R212.1
TXS2: C210.1, R212.2, U202.3 (+)
TX_B1: C318.2, C319.1, CT304.1, L306.1
TX_B2: C319.2, C320.1, CT305.1, L307.1
TX_B3: C320.2, C321.1, CT306.1, L308.1
TX_OUT: C327.1, D601.2 (A), L312.2, L602.2
TX_T1: C312.2, C313.1, CT302.1, L302.1
TX_T2: C315.2, C316.1, CT303.1, L304.1
TX_X3_B: C305.2, Q302.3 (B), R304.2, R305.1
TX_X3_C: C312.1, L301.2, Q302.1 (C)
TX_X3_E: C306.1, Q302.2 (E), R306.1
TX_X3_VC: C307.1, L301.1, R304.1, R307.2
TX_X6_B: C313.2, Q303.1 (B), R308.2, R309.1
TX_X6_C: C315.1, L303.2, Q303.3 (C)
TX_X6_E: C308.1, Q303.2 (E), R310.1
TX_X6_VC: C309.1, L303.1, R308.1, R311.2
TX_X12_B: C316.2, Q304.1 (B), R312.2, R313.1
TX_X12_C: C318.1, L305.2, Q304.3 (C)
TX_X12_E: C310.1, Q304.2 (E), R314.1
TX_X12_VC: C311.1, L305.1, R312.1, R315.2
V5R: C106.1, R402.1, R404.1, R405.1, R408.1, U102.1 (VO)
V5T: C104.1, C304.1, Q301.3 (C), R203.1, R207.1, R301.1, U101.1 (VO)
V9: C101.1, C102.1, D101.1 (K), SW102.2 (B)
VAR: CT301.1, D301.1 (K), R205.2, R206.2, Y301.2
VBAT: J101.1, SW101.2 (B)
VBAT_ON: D101.2 (A), SW101.1 (A)
VBIAS: C204.1, R206.1, R207.2, R208.1
VOL_TOP: C507.2, RV501.3
VOL_W: C508.2, RV501.2
VREF_R: C501.1, R501.2, R502.1, R503.2, R508.2
VREF_T: C201.1, R201.2, R202.1, R204.2
V_RX: C105.1, C107.1, C512.1, C513.1, C514.1, Q501.2 (C), R501.1, R509.1, SW102.1 (A), U102.3 (VI), U501.7 (V+), U502.7 (V+), U503.7 (V+)
V_TX: C103.1, C208.1, C211.1, R201.1, R307.1, R311.1, R315.1, R319.1, R601.1, SW102.3 (C), U101.3 (VI), U201.7 (V+), U202.7 (V+)
XB: C302.1, Q301.2 (B), R301.2, R302.1, Y301.1
XE: C302.2, C303.1, C305.1, Q301.1 (E), R303.1
ZOB: C511.1, R515.2

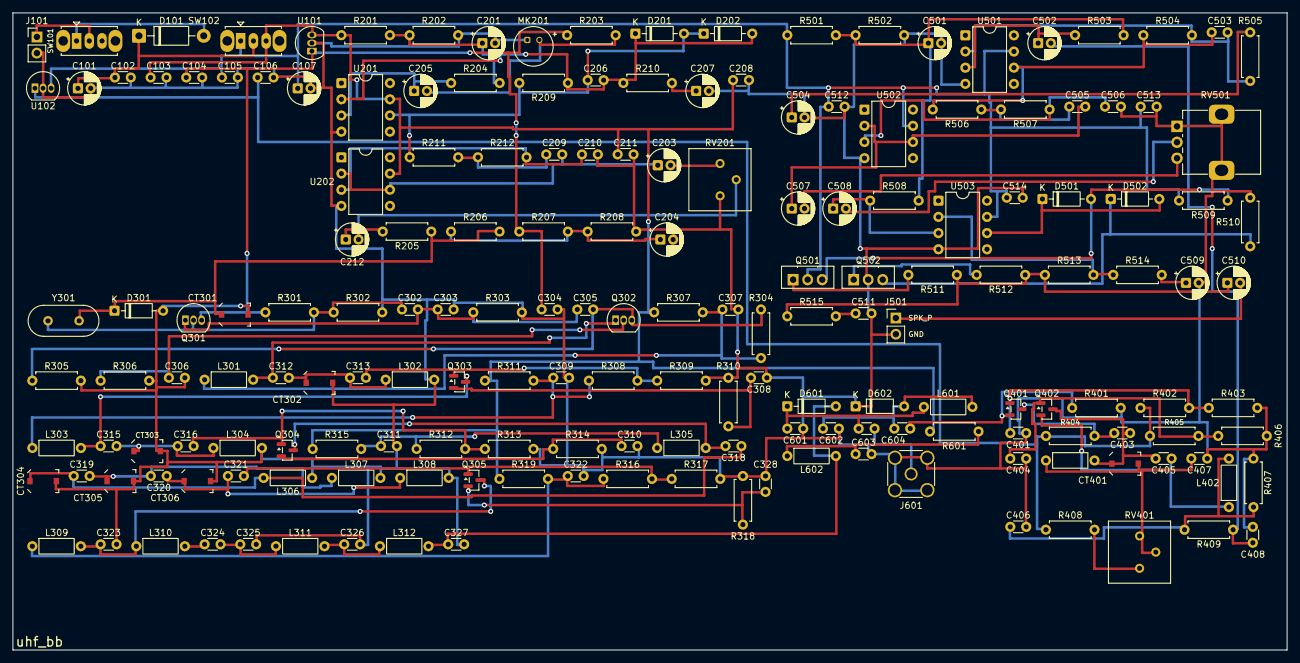
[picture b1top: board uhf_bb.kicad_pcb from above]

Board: 2 copper layers, 200.0 x 100.0 mm, 182 parts (0 on the bottom side), 84 nets.
